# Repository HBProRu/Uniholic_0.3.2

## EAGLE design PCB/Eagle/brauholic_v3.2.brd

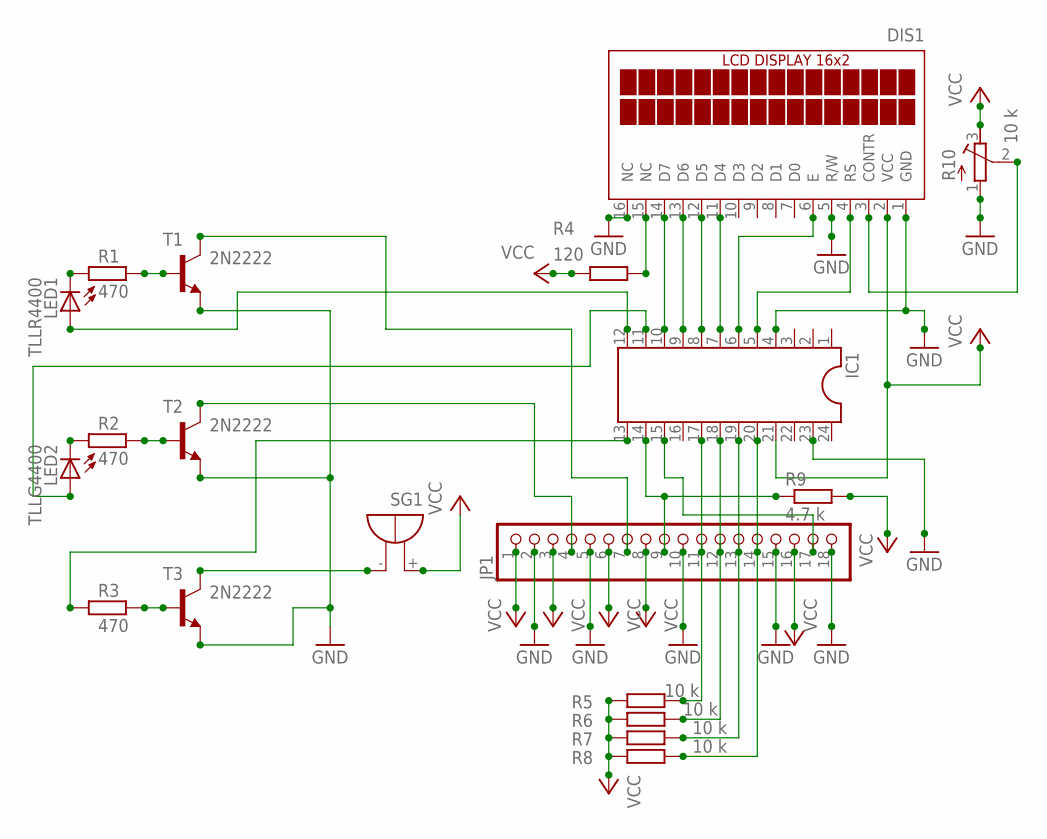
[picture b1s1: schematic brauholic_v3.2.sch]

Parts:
DIS1: TUXGR_16X2_R2
IC1: DIL24-6
JP1: PINHD-1X18; 1X18
LED1: TLLR4400; LED3MM
LED2: TLLG4400; LED3MM
R1, R2: 470; 0207/10
R3: 470; 0207/12
R4: 120; 0207/10
R5, R6, R7, R8: 10 k; 0207/10
R9: 4.7 k; 0207/12
R10: 10 k; RTRIM3339P
SG1: F/TMB
T1, T2, T3: 2N2222; TO92-EBC

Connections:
GND: DIS1.1 (GND), DIS1.5 (R/W), DIS1.16 (NC), IC1.4, IC1.23, JP1.2, JP1.5, JP1.10, JP1.15, JP1.18, R10.1 (E), T1.E, T2.E, T3.E
unnamed: R1.2, T1.B
unnamed: R2.2, T2.B
unnamed: R3.2, T3.B
unnamed: IC1.12, LED1.A
unnamed: LED1.K (C), R1.1
unnamed: IC1.13, R3.1
unnamed: DIS1.14 (D7), IC1.10
unnamed: DIS1.13 (D6), IC1.9
unnamed: DIS1.12 (D5), IC1.8
unnamed: DIS1.11 (D4), IC1.7
unnamed: SG1.-, T3.C
unnamed: IC1.11, LED2.A
unnamed: LED2.K (C), R2.1
unnamed: JP1.7, T1.C
unnamed: JP1.4, T2.C
unnamed: IC1.14, JP1.9, R9.1
unnamed: DIS1.15 (NC), R4.2
unnamed: IC1.18, JP1.12, R6.2
unnamed: DIS1.3 (CONTR), R10.2 (S)
unnamed: IC1.17, JP1.11, R5.2
unnamed: IC1.15, JP1.17
unnamed: IC1.19, JP1.13, R7.2
unnamed: IC1.20, JP1.14, R8.2
unnamed: DIS1.6 (E), IC1.6
unnamed: DIS1.4 (RS), IC1.5
VCC: DIS1.2 (VCC), IC1.21, JP1.1, JP1.3, JP1.6, JP1.8, JP1.16, R4.1, R5.1, R6.1, R7.1, R8.1, R9.2, R10.3 (A), SG1.+

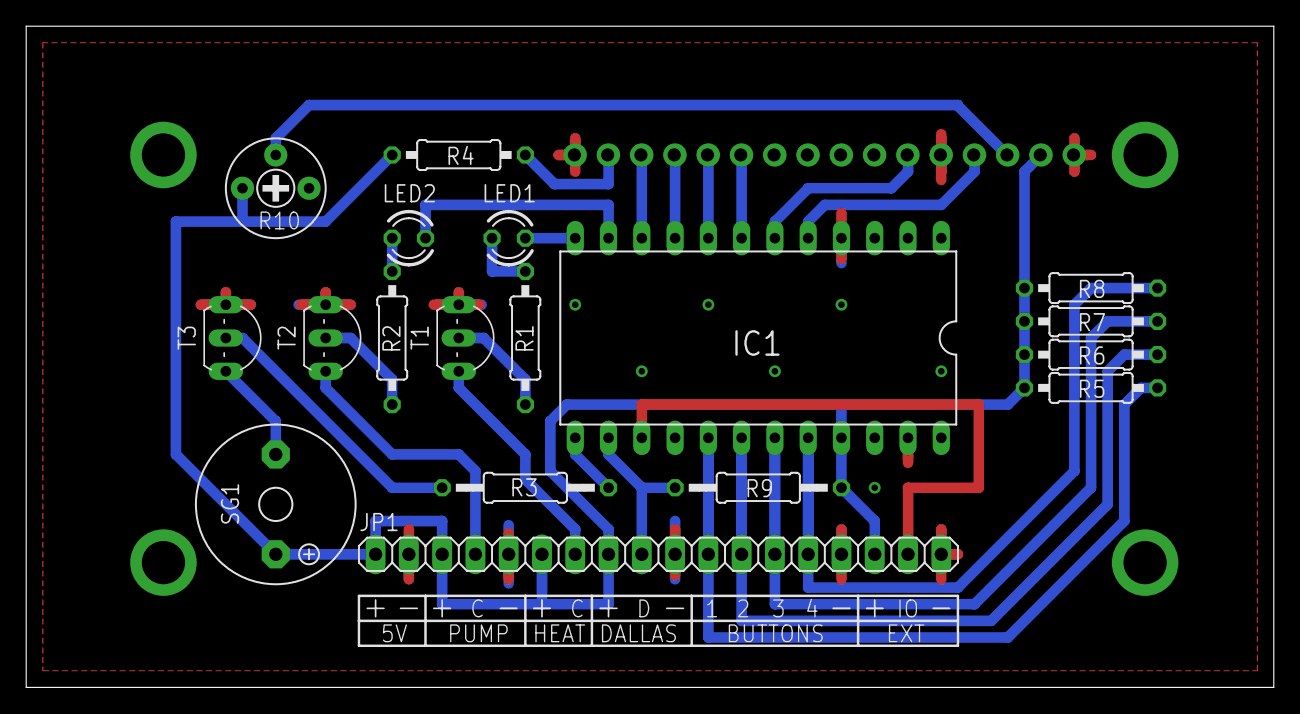
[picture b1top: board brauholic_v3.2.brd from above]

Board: 2 copper layers, 95.2 x 50.5 mm, 19 parts (1 on the bottom side), 27 nets.

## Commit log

2015-12-09 Add files
